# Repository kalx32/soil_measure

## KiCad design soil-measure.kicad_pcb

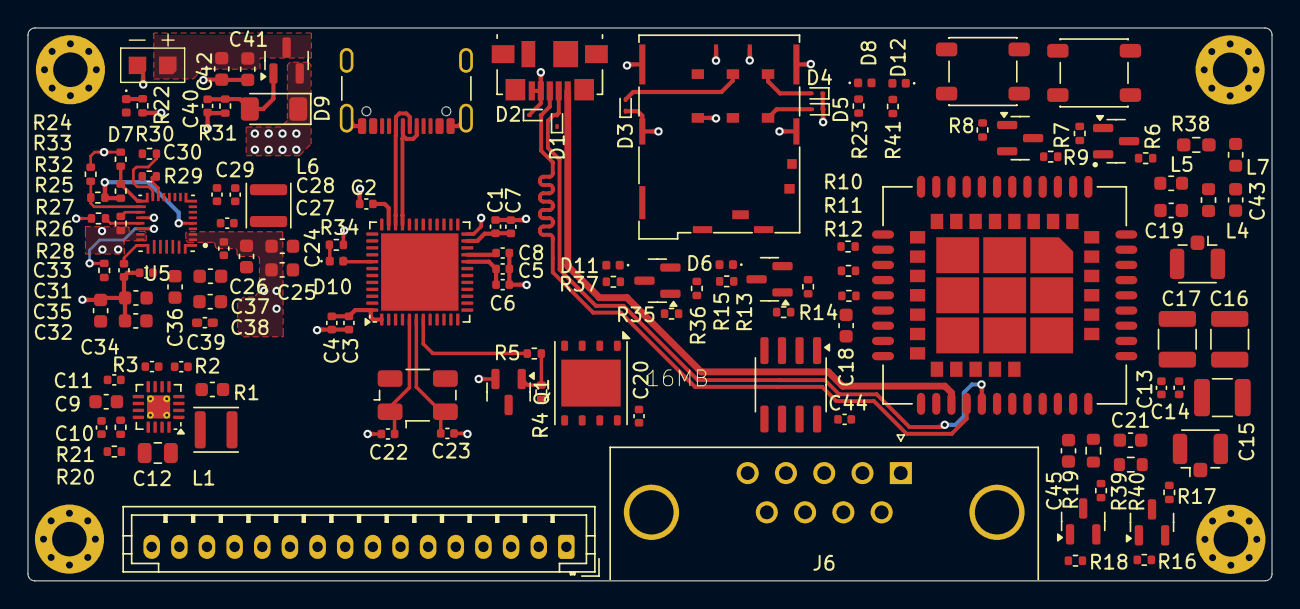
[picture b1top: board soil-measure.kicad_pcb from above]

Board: 4 copper layers, 90.0 x 40.0 mm, 132 parts (0 on the bottom side), 109 nets.

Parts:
C1, C2, C3, C5, C13, C20, C44: 100n; C_0402_1005Metric
C4, C30: 4u7; C_0402_1005Metric
C6, C8, C14: 1u; C_0402_1005Metric
C7: 10n; C_0402_1005Metric
C9, C24, C25, C26, C32, C33, C34, C36, C37, C38, C41, C42: 10u; C_0603_1608Metric
C10, C27, C35: 0.1u; C_0402_1005Metric
C11: 3n3; C_0402_1005Metric
C12: 22u; C_0805_2012Metric
C15, C16, C17: 100u; C_1210_3225Metric
C18: 100n; C_0603_1608Metric
C19, C21, C43, C45: C; C_0603_1608Metric
C22, C23: 8p; C_0402_1005Metric
C28, C29: 47n; C_0402_1005Metric
C31: 1n; C_0402_1005Metric
C39: 0.1u; C_0402_1005Metric_Pad0.74x0.62mm_HandSolder
C40: 22p; C_0402_1005Metric
D1, D2, D3, D4, D5: ESD9B5.0ST5G; D_SOD-923
D6, D7, D8, D10, D11, D12: LED; LED_0402_1005Metric
D9: BZV55B5V1; D_MiniMELF
H1, H2, H3, H4: MountingHole; MountingHole_2.5mm_Pad_Via
J1: JAE_SIM_Card_SF72S006
J2, J4: Conn_Coaxial; U.FL_Hirose_U.FL-R-SMT-1_Vertical
J3: USB_B; USB_Micro-B_Molex_47346-0001
J5: USB_C_Receptacle_USB2.0_14P; USB_C_Receptacle_GCT_USB4105-xx-A_16P_TopMnt_Horizontal
J6: DE9_Socket_MountingHoles; DSUB-9_Socket_Horizontal_P2.77x2.84mm_EdgePinOffset4.94mm_H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
J7: Conn_01x16; JST_PH_B16B-PH-K_1x16_P2.00mm_Vertical
L1: 2u2; L_APV_ANR3010
L4, L5: L; L_0603_1608Metric
L6: 1u; L_APV_ANR3010
L7: 47n; L_0603_1608Metric
Q1, Q2, Q3, Q4, Q5, Q6, Q8: SS8050; SOT-23
Q7: AO3401A; SOT-23
R1: 100k; C_0603_1608Metric
R2: 178k; C_0402_1005Metric
R3: 51k; C_0402_1005Metric
R4: 47K; R_0402_1005Metric
R5: 4K7; R_0402_1005Metric
R6, R9, R17, R19, R24, R28, R29, R30: 10k; R_0402_1005Metric
R7, R8, R13, R16, R18, R35: 4k7; R_0402_1005Metric
R10, R11, R12: 22R; R_0402_1005Metric
R14, R36: 47k; R_0402_1005Metric
R15, R37, R41: 510R; R_0402_1005Metric
R20, R21, R22, R34: R; R_0402_1005Metric
R23: 2k2; R_0402_1005Metric
R25: 5K24; R_0402_1005Metric
R26: 10k5; R_0402_1005Metric
R27: 100R; R_0402_1005Metric
R31: 220R; R_0402_1005Metric
R32: 127k; R_0402_1005Metric
R33: 100k; R_0402_1005Metric
R38: 10R; R_0603_1608Metric_Pad0.98x0.95mm_HandSolder
R39, R40: R; R_0603_1608Metric
SW1, SW2: SW_SPST; SW_SPST_PTS647_Sx38
U1: STM32G431CBUx; QFN-48-1EP_7x7mm_P0.5mm_EP5.6x5.6mm
U2: TPS62130; VQFN-16-1EP_3x3mm_P0.5mm_EP1.68x1.68mm_ThermalVias
U3: SIM7080G; XCVR_SIM7080G
U4: W25Q128JVP; WSON-8-1EP_6x5mm_P1.27mm_EP3.4x4.3mm
U5: BQ25672RQMR; IC_BQ25672RQMR
U6: ISL3172E; SOIC-8_3.9x4.9mm_P1.27mm
U7: BAT
Y1: 8MHz; Crystal_SMD_Abracon_ABM3B-4Pin_5.0x3.2mm

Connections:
+3V6: C1.1, C2.1, C3.1, C4.1, C5.1, C6.1, C7.1, C8.1, C12.1, C13.1, C14.1, C15.1, C16.1, C17.1, C20.1, C44.1, D7.2 (A), J1.CSW, J7.2, J7.14, L1.2, R1.2, R2.1, R6.1, R15.1, R17.1, R28.1, R29.1, R30.1, R37.1, R38.2, U1.1 (VBAT), U1.20 (VREF+), U1.21 (VDDA), U1.23 (VDD), U1.35 (VDD), U1.48 (VDD), U2.14 (VOS), U3.34 (VBAT), U3.35 (VBAT), U4.8 (VCC), U6.8 (VCC)
+12V: C9.1, C10.1, C32.1, C33.1, C34.1, C35.1, R20.1, U2.10 (VIN), U2.11 (VIN), U2.12 (VIN), U5.25 (SYS)
/BATT: R20.2, R21.1, U1.8 (PA0), U2.13 (EN)
/CC1: J5.A5 (CC1), U1.44 (PB6)
/CC2: J5.B5 (CC2), U1.42 (PB4)
/CHG_EN: U1.4 (PC15), U5.13 (CE_N)
/CHG_SCL: R29.2, U1.38 (PA15), U5.14 (SCL)
/CHG_SDA: R30.2, U1.45 (PB7), U5.15 (SDA)
/DATA_CMD: J7.8, U1.40 (PC11)
/DEBUG_LED: D10.2 (A), U1.41 (PB3)
/DISP_EN: J7.9, U1.2 (PC13)
/FBK: R2.2, R3.1, U2.5 (FB)
/GNSS_RX: Q8.2 (E), U1.16 (PC4)
/GNSS_TX: Q6.3 (C), R17.2, U1.32 (PA10)
/HOLD: U1.9 (PA1), U4.7 (~HOLD/~RESET/IO_{3})
/I2C2_SCL: J7.12, U1.31 (PA9)
/I2C2_SDA: J7.13, U1.30 (PA8)
/MCU_DN: J5.A7 (D-), J5.B7 (D-), U1.33 (PA11)
/MCU_DP: J5.A6 (D+), J5.B6 (D+), U1.34 (PA12)
/MODEM_INT: U1.47 (PB9), U3.7 (UART1_RI)
/MOD_RX: Q5.2 (E), U1.10 (PA2)
/MOD_TX: Q4.3 (C), R6.2, U1.11 (PA3)
/PWR_CTR: R5.1, U1.7 (PG10)
/RST: J7.7, U1.39 (PC10)
/SHIP_MODE: U1.3 (PC14), U5.12 (QON_N)
/SPI1_CLK: U1.13 (PA5), U4.6 (CLK)
/SPI1_MISO: U1.14 (PA6), U4.2 (DO/IO_{1})
/SPI1_MOSI: U1.15 (PA7), U4.5 (DI/IO_{0})
/SPI1_NSS: U1.12 (PA4), U4.1 (~CS)
/SPI2_CLK: J7.3, U1.26 (PB13)
/SPI2_MISO: J7.5, U1.27 (PB14)
/SPI2_MOSI: J7.4, U1.28 (PB15)
/SPI2_NSS: J7.6, U1.25 (PB12)
/SWDCLK: J7.16, U1.37 (PA14)
/SWDIO: J7.15, U1.36 (PA13)
/TIM8_PWM: J7.10, U1.29 (PC6)
/TXM: J6.2, U6.7 (B)
/TXP: J6.3, U6.6 (A)
/UART3_DE: U1.19 (PB2), U6.3 (DE)
/UART3_RE: U1.18 (PB1), U6.2 (~RE)
/UART3_RX: U1.24 (PB11), U6.1 (RO)
/UART3_TX: U1.22 (PB10), U6.4 (DI)
/WP: U1.17 (PB0), U4.3 (~WP/IO_{2})
/battery_charger/ILIM: R32.2, R33.1, U5.17 (ILIM_HIZ)
/battery_charger/PMID: C36.1, C37.1, C38.1, C39.1, U5.29 (PMID)
/battery_charger/TS: R24.1, R25.2, U5.16 (TS)
/battery_charger/VIN_P: C41.1, C42.1, Q7.3 (D), U7.1 (+V)
/cellular_interface/CARD_DT: J1.DSW, R41.1
/cellular_interface/DN: D1.2 (A2), J3.2 (D-), U3.26 (USB_DM)
/cellular_interface/DP: D2.2 (A2), J3.3 (D+), U3.25 (USB_DP)
/cellular_interface/GPS_RX: Q8.3 (C), R19.1, U3.62 (UART3_RXD)
/cellular_interface/GPS_TX: Q6.2 (E), U3.61 (UART3_TXD)
/cellular_interface/MODEM_STAT: R13.2, U3.42 (STATUS)
/cellular_interface/NET_STAT: R35.2, U3.41 (NETLIGHT)
/cellular_interface/PWR: Q1.3 (C), U3.39 (PWRKEY)
/cellular_interface/SIM_CLK: R11.2, U3.16 (SIM_CLK)
/cellular_interface/SIM_RST: R12.2, U3.17 (SIM_RST)
/cellular_interface/UART_RX: Q5.3 (C), R9.1, U3.2 (UART1_RXD)
/cellular_interface/UART_TX: Q4.2 (E), U3.1 (UART1_TXD)
/cellular_interface/USB_BOOT: SW2.2 (B), U3.20 (USB_BOOT)
CHG_INT: R28.2, U5.21 (INT_N)
GND: C1.2, C2.2, C3.2, C4.2, C5.2, C6.2, C7.2, C8.2, C9.2, C10.2, C11.2, C12.2, C13.2, C14.2, C15.2, C16.2, C17.2, C18.2, C20.2, C21.2, C22.2, C23.2, C24.2, C25.2, C26.2, C27.2, C30.2, C31.1, C32.2, C33.2, C34.2, C35.2, C36.2, C37.2, C38.2, C39.2, C40.2, C41.2, C42.2, C44.2, C45.2, D1.1 (A1), D2.1 (A1), D3.1 (A1), D4.1 (A1), D5.1 (A1), D12.1 (K), J1.C5 (GND), J1.SH, J2.2 (Ext), J3.4 (GND), J3.5 (Shield), J4.2 (Ext), J5.A1 (GND), J5.A12 (GND), J5.B1 (GND), J5.B12 (GND), J5.S1 (SHIELD), J6.0 (PAD), J6.5, J7.1, J7.11, L4.1, L5.2, Q1.2 (E), Q2.2 (E), Q3.2 (E), R3.2, R4.2, R14.2, R21.2, R22.2, R24.2, R26.2, R31.2, R33.2, R34.2, R36.2, SW1.1 (A), SW2.1 (A), U1.46 (PB8), U1.49 (VSS), U2.6 (GND), U2.7 (FSW), U2.8 (DEF), U2.15 (GND), U2.16 (GND), U2.17 (GND), U3.8 (GND), U3.13 (GND), U3.19 (GND), U3.21 (GND), U3.27 (GND), U3.30 (GND), U3.31 (GND), U3.33 (GND), U3.36 (GND), U3.37 (GND), U3.45 (GND), U3.63 (GND), U3.66 (GND), U3.67 (GND), U3.69 (GND), U3.70 (GND), U3.71 (GND), U3.72 (GND), U3.73 (GND), U3.74 (GND), U3.75 (GND), U3.76 (GND), U3.77 (GND), U4.4 (GND), U5.10 (ACDRV2), U5.11 (ACDRV1), U5.27 (GND), U6.5 (GND), U7.2 (-v)
MOD_VBUS: J3.1 (VBUS), U3.24 (USB_VBUS)
unnamed: C19.2, C43.1, L4.2
unnamed: C45.1, R39.2, R40.1
unnamed: D3.2 (A2), J1.C2 (RST), R12.1
unnamed: D4.2 (A2), J1.C3 (CLK), R11.1
unnamed: D6.2 (A), R15.2
unnamed: D6.1 (K), Q2.3 (C)
unnamed: D7.1 (K), R22.1
unnamed: D8.1 (K), R23.2
unnamed: C40.1, D9.2 (A), Q7.1 (G), R31.1
unnamed: D10.1 (K), R34.1
unnamed: D11.2 (A), R37.2
unnamed: D11.1 (K), Q3.3 (C)
unnamed: D12.2 (A), R41.2
unnamed: J2.1 (In), R40.2
unnamed: C43.2, J4.1 (In), L7.2
unnamed: L1.1, U2.1 (SW), U2.2 (SW), U2.3 (SW)
unnamed: L7.1, R38.1
unnamed: Q1.1 (B), R4.1, R5.2
unnamed: Q2.1 (B), R13.1, R14.1
unnamed: Q3.1 (B), R35.1, R36.1
unnamed: Q4.1 (B), R7.2
unnamed: Q5.1 (B), R8.1
unnamed: Q6.1 (B), R16.2
unnamed: Q8.1 (B), R18.1
unnamed: SW1.2 (B), U1.43 (PB5)
unnamed: C22.1, U1.5 (PF0), Y1.1
unnamed: C23.1, U1.6 (PF1), Y1.2
unnamed: R1.1, U2.4 (PG)
unnamed: C11.1, U2.9 (SS/TR)
unnamed: C19.1, L5.1, U3.68 (GNSS_ANT)
unnamed: C21.1, R39.1, U3.32 (RF_ANT)
unnamed: R10.2, U3.15 (SIM_DATA)
unnamed: R27.1, U5.18 (BATP)
unnamed: C28.1, U5.4 (BTST1)
unnamed: C29.1, L6.2, U5.19 (BTST2)
unnamed: R26.1, U5.20 (PROG)
unnamed: C31.2, U5.24 (SDRV)
unnamed: R23.1, U5.1 (STAT)
unnamed: C28.2, L6.1, U5.28 (SW1)
unnamed: C29.2, U5.26 (SW2)
REGN: C30.1, D8.2 (A), R25.1, R32.1, U5.5 (REGN)
SIM_DATA: D5.2 (A2), J1.C7 (I/O), R10.1
SIM_VDD: C18.1, J1.C1 (VCC), U3.18 (SIM_VDD)
VBATP: D9.1 (K), Q7.2 (S), R27.2, U5.22 (BAT), U5.23 (BAT)
VBUS: C24.1, C25.1, C26.1, C27.1, J5.A4 (VBUS), J5.A9 (VBUS), J5.B4 (VBUS), J5.B9 (VBUS), U5.2 (VBUS), U5.3 (VBUS), U5.8 (VAC2), U5.9 (VAC1)
VDD_EXT: R7.1, R8.2, R9.2, R16.1, R18.2, R19.2, U3.40 (VDD_EXT)

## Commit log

2025-08-05 adding schematic design pdf
2025-08-05 added kicad files containing schematic design and PCB layout
2025-08-06 Assigned footprints in the schematic, added comments and mounting holes
2025-08-10 PCB files added, some comments in the schematic
2025-08-10 Fixed bug on schematic
2025-08-15 changed footprint for component BQ25672RQMR and routed a controlled impedance trace over the USB interfaces, at 90ohm DI
2025-08-15 Removed redundant files
